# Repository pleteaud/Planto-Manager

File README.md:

# Planto-Manager

## Description: 
This is an embedded project aimed at monitoring and caring for a potted plant. Device is able to monitor room temperature and humidity using the [DHT11](https://www.adafruit.com/product/386). It can also measure the soil moisture by utilizing a personally designed soil moisture sensor, influenced by [Grove's Capacitor Soil Moisture Sensor](https://wiki.seeedstudio.com/Grove-Capacitive_Moisture_Sensor-Corrosion-Resistant/). Additionally, the device is able to track time and set alarms using the [DS3231](https://components101.com/modules/ds3231-rtc-module-pinout-circuit-datasheet) RTC module. A [16x2 Character LCD](https://www.sparkfun.com/products/709)  was used to display relevant information. Lastly, given the simplicity of the tasks and the low cost, the firmware was developed on an Atmega328P.

## Libraries:
  [Atmel Start Configuration Files](https://start.atmel.com/#dashboard)

## Images:

### Planto Manager System 

### Planto Manager System Wiring

### Soil Moisture Sensor PCB Layout

### Soil Moisture Sensor Reading (Dry Case)
.jpg)

### Soil Moisture Sensor Reading (Moist Case)
.jpg)

## Future Plan
- [ ] Switch to Adafruit BME280 sensor since it supports I2C. This will free up pins and reduce the timing issues faced with the DHT11
- [ ] Implement a Keypad module to allow user to inter inferace with device out of debug mode.
- [ ] Fix Soil moisture sensor code bugs.
- [ ] Implement I2C I/O Expander (MCP23017-E/SP-ND) to reduce number of pins used by the LCD and Keypad
- [ ] Implement reworks and design upgrades to Soil Moisture Sensor
- [ ] Design and build container for device

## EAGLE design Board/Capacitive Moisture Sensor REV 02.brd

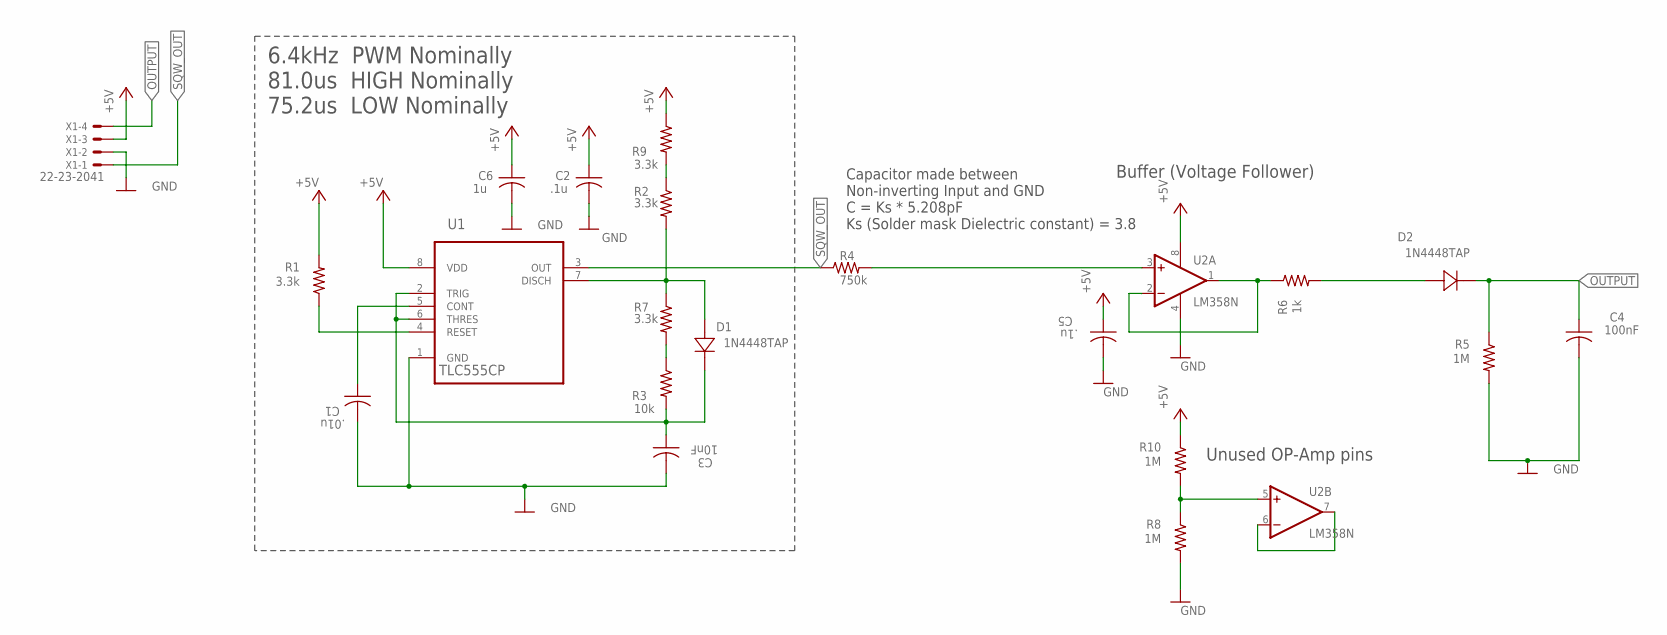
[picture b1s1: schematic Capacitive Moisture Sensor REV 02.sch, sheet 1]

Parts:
C1: .01u; C1206
C2, C5: .1u; C1206
C3: 10nF; C1206
C4: 100nF; C1206
C6: 1u; C1206
D1, D2: 1N4448TAP; DO-35
R1, R2, R7, R9: 3.3k; R1206
R3: 10k; R1206
R4: 750k; R1206
R5, R8, R10: 1M; R1206
R6: 1k; R1206
U1: TLC555CP; DIP254P762X508-8
U2: LM358N; DIL08
X1: 22-23-2041

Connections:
+5V: C2.1, C5.1, C6.1, R1.2, R9.1, R10.1, U1.8 (VDD), U2.8 (V+), X1.3
GND: C1.2, C2.2, C3.2, C4.2, C5.2, C6.2, R5.2, R8.2, U1.1 (GND), U2.4 (V-), X1.2
unnamed: U2.6 (-IN), U2.7 (OUT)
unnamed: C3.1, D1.1, R3.2, U1.2 (TRIG), U1.6 (THRES)
unnamed: R1.1, U1.4 (RESET)
unnamed: C1.1, U1.5 (CONT)
unnamed: D2.2, R6.2
unnamed: R3.1, R7.2
unnamed: R4.2, U2.3 (+IN)
unnamed: R2.1, R9.2
unnamed: R6.1, U2.1 (OUT), U2.2 (-IN)
unnamed: D1.2, R2.2, R7.1, U1.7 (DISCH)
unnamed: R8.1, R10.2, U2.5 (+IN)
OUTPUT: C4.1, D2.1, R5.1, X1.4
SQW_OUT: R4.1, U1.3 (OUT), X1.1

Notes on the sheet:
Buffer (Voltage Follower)
6.4kHz PWM Nominally 81.0us HIGH Nominally 75.2us LOW Nominally
Capacitor made between Non-inverting Input and GND C = Ks * 5.208pF Ks (Solder mask Dielectric constant) = 3.8
Unused OP-Amp pins

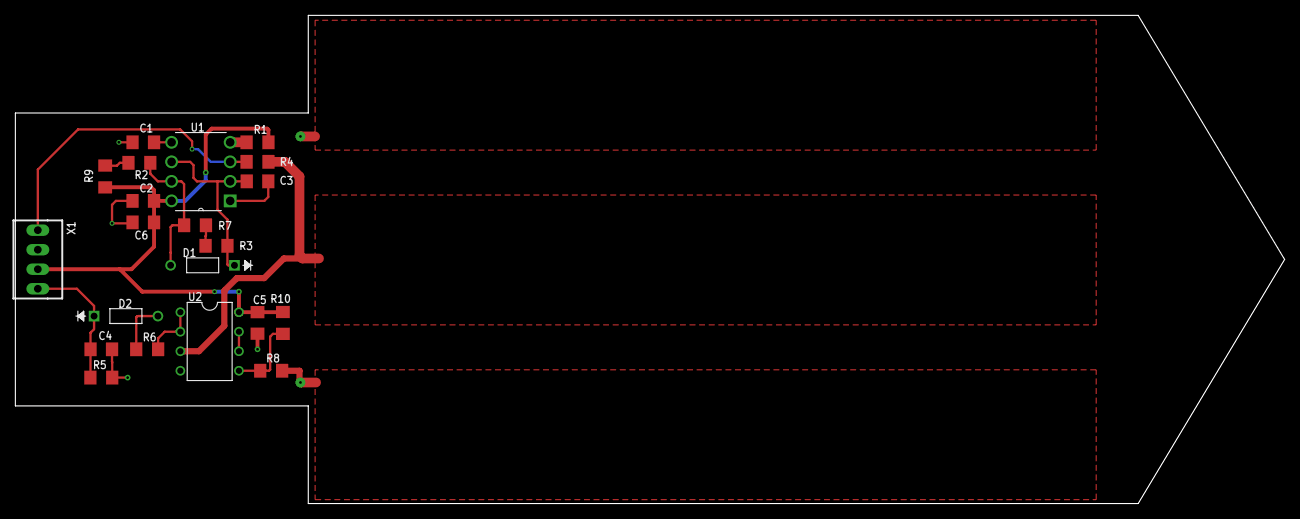
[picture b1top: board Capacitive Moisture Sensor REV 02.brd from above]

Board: 2 copper layers, 165.1 x 63.5 mm, 22 parts (0 on the bottom side), 15 nets.

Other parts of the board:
DRILEGEND: DRILEGEND

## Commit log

2019-08-10 Initial source code for PM
2019-08-16 initial version of interrupt routine
2019-08-16 Created initial version of i2c manager object. Currently, there's only helper functions, but in a week I'll add the struct
2019-08-16 modified the name and organization of flag macros for easier use.
2019-08-16 Added functions to transfer control of buffer to either slave or master
2019-08-18 Redefined and organized mask macros. Modified configPayload toonly take a alarm object. Added a function to configure alarm matching conditions. Completed alarmsPoll function. Updated payload configu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
2019-08-18 Cleaned up the alarm object by combining flags and states into one variable. Added a matching configuration flag. Enumerated the matching options.
2019-08-18 added a dy_dt alarm flag. Added a function to retrieve the alarm match flag
2019-08-18 added a function to set rtc device's control register.Lenght of commands are now calculated using sizeof __cmdType__
2019-08-18 Change name of rtcUpdateCtrlReg to rtcSetCtrlReg
2020-05-19 Project Document
2020-05-19 IC datasheets
2020-05-19 Board Layout and Schematic
2020-05-19 Temperature and Moisture sensor code added
2020-05-19 Remove duplicates
2020-05-19 Removing duplicates
2020-05-19 Revert "Temperature and Moisture sensor code added"
    This reverts commit 3d2d300fd749efcdf5ff3812b05353742edbb3e9.
2020-05-19 xRevert "Revert "Temperature and Moisture sensor code added""
    This reverts commit 201d351d41fd05fb5b25cc0a1de2bad0640da718.
2020-05-19 reupload of deleted files
2020-05-20 Tweaked method to initiate temp/hum reading. Added function to turn on or off relay. Tweaked buggs
2020-05-29 Made modification and reworks after testing and debugging board
2020-05-29 Datasheet for LM358 op-amp
2020-05-29 Completed board layout for rework modification
2020-05-29 removed duplicates
2020-07-08 Create DHT11-Technical-Data-Sheet-Translated-Version-1143054.pdf
    Added DHT11 Sensor Datasheet
2020-07-08 Cleaned up Code
    Added comments describing functions and rename certain structs/functions for easier understanding
2020-07-11 Added Sensor Calibration Function
    -Added sensor calibration function
    -Designed output moisture value to be between 0-100
2020-07-11 Moved 4s delay to dht init function
2020-08-08 Update DS3231.pdf
    Datasheet for DS3231 RTC Timer
2020-08-08 Updated Atmel Start Include and Source
2020-08-08 Updated Alarm Object
    Alarm Object does not have the ability to initiate a command no more. It's responsibility is to simply initialize and set is time array and callback function
2020-08-08 Increased Buffer Size
2020-08-08 Update ds3231_regs_and_utils.h
    Added the flags for alarm register mask bit
2020-08-08 Created I2C control Code.
    Will update with I2C object if I feel the Atmega code doesn't suffice
2020-08-08 Updated RTC code
    -Moved all command intiation and preparation function to withing RTC object's control. (Alarm object can no longer initiate the command to set Alarm registers).
    -Added a state machine and polling function for RTC
    -Reduce number of commands to 6: set alarm 1 and 2, set control register, set status register, set time, read all registers.
    -Future updates will add more command
2020-08-08 Update driver_isr.c
    Added an interrupt vector for external interrupts
2020-08-08 Update main.c
    Configured Main C to initialize, configure, and poll RTC
2020-08-14 Update alarm.c
    Added a callback function check; only execute said function if it's not null
2020-08-14 Updated DHT11 interface
    Cleaned up code.
    Implemented a different algorithm to execute communication with dht11. library which i based this logic is referenced in code
2020-08-14 Update driver_isr.c
    Removed External Pin interrupt.
2020-08-14 Update ds3231_regs_and_utils.h
    Code clean up
2020-08-14 Update i2cMasterControl.c
    Added header to file to get rid of indirect reference to functions in cmd_proc
2020-08-14 LCD Interface Code
    Developed firmware to interface with DHT11
2020-08-14 Create Planto Manager.atsln
    Added atmel solution
2020-08-14 Updated RTC interface firmware
    -Added enum for months
    -Altered process of updating time and handling alarm interrupts. Instead of using external interrupts, we are simply going to poll the INT pin state. I've made this change because, most of the times 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
    -Added LCD interface code to print out time
2020-08-14 Update driver_init.c
    Removed External interrupts. No longer needed
2020-08-14 Update i2c_master.c
    Accidently modified this function. it should be reset
2020-08-14 Updated Timer Control
    Update Timer values to reflect the change I made to the CPU frequency (now 16MHz)
2020-08-14 Added LCD Datasheet
2020-08-14 Create main.h
    Added a main.h to store all headers that's going to be used in main.c
2020-08-14 Update main.c
    Configured Main.c to use all objects except soil moisture. Will add this tomorrow
2020-08-14 Removed EXT INT code
2020-08-14 Changed clock speed to 16MHz
2020-08-14 Delete Problem.docx
    Not relevant to this project anymore. Decided to reduce the scale. Also it's still a rough draft. I will upload a more thourough and complete draft once I have acquired enough time to think through t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
2020-08-15 Update DHT11.c
    Moved location where data is printed on LCD screen
2020-08-15 Update LCD.c
    Took out the unused parameter in LCD code
2020-08-15 Create Typical Questions and Challenges and Solution.docx
    Some of the challenges or question i had while working on this project. will add the adversities I experienced with the EE side of things later
2020-08-15 Update rtc.c
    Fixed location where data is printed on the LCD screen
2020-08-15 Integrated Soil Moisture
    -Unfortunately my Xplained board broke. I need to get a new one to completely test and debug the intergration.
2020-08-18 Files are not pertinent to this project
2020-08-20 Soil Moisture Simulation File
2020-08-20 Create TLC555astable.xls
    Updated version of Astable 555 timer calculator sheet
2020-08-20 Updated text in schematic
2020-08-20 Board Schematic and Layout pictures
2020-08-21 Added description to schematic
2020-08-21 Created a Planto Manager Eagle Project
2020-08-21 Created a wiring schematic of all the modules in the project
2020-08-24 Create Planto Manager Modules Connected.jpg
    Picture of all the modules of the project connected. Did not print the reading from soil moisture sensor since it's been buggy.
2020-08-24 changed relay and dht11 pins
2020-08-24 Changed pins
2020-08-24 Removed call to lcdreturnhome()
    it was unecessary
2020-08-24 Changed TCNT value to get timer to be more accurate
2020-08-24 Updated Moisture Sensor Methods and Structure
    -House Keeping
    -Changed pin for relay control
    - Switching to blocking method for reading sensor as opposed to non-blocking (polling/interrupts) since currently our code is breaking using that method.
    - There is a frustrating bug with the software written for the soil moisture. For some unknown reason the I can debug correctly when using it. Furthermore the readings are inaccurate. I suspect my ma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
2020-08-24 Added some LCD prints to indicate object initializations
    -removed calls to sensor object. It seems to be breaking the code.
2020-08-24 Moved Atmel Start files to a different folder
2021-01-03 Moved header and source files to approriate folder
2021-01-03 Added the BME280 Driver Library
2021-01-03 No use for this object
2021-01-03 No used for this object. Switched to BME280 sensor
2021-01-03 Deleted because the correct file is "i2cMasterControl"
2021-01-03 Folder Rename
2021-01-03 Moved header file
2021-01-03 Designed LCD object. Added public interfaces
    Switched to LCD-1602CA
2021-01-03 Created main.h
2021-01-03 Developed mcp23017 object. Added public interfaces
2021-01-03 Modified the rtc object and its public interfaces.
2021-01-03 housekeeping
2021-01-06 Changed signature of delay functions to unsigned
2021-01-06 Made an error flag the output of trasmit and read functions.
2021-01-06 Using 64 bit mode
2021-01-06 Iplemented the printing methods for time, temperature, and humidity
    Added support for the BME sensor
2021-01-06 Removed unecessary headers
2021-01-07 Added an MCP object pointer as a data member
2021-01-07 Initilized the mcp object in main and passed to the lcd object to communicate via i2c
2021-01-07 Fixed the inccorect initialization of array
2021-01-08 Changed name of class to ds3231
    Updated name of functions to match new class name
    Updated name of enums
2021-01-08 Changed signatures of functions / housekeeping
    -Added const modifer where appropriate
    -Changes size of error list
2021-01-08 Updated main.h to reflect new class name
2021-01-08 Updated function name to reflect class name
2021-01-18 Added code to poll a 4x4 keypad module
2021-01-24 made a typedef for the time units enum
2021-01-24 Added function to verify time
2021-01-24 Added function to allow user to set time && print error encounted
